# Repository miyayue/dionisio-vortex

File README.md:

# Projeto Dionísio
Esse projeto de IoT é o desafio de treinamento do laboratório de formação e inovação Vortex. O desafio consiste em construir uma mini adega de vinho inteligente, em que o usuário possa monitorar a temperatura e umidade dentro da adega e com controle de acesso por RFID ou controle remoto através de um Dashboard.

# Instruções
## Firmware
No VSCode, instale a extensão `PlatformIO`. Modifique os valores das variáveis `ssid` e `pswd` para o nome de sua rede WiFi e senha, respectivamente. Salve o arquivo e rode o comando `Upload and Monitor` para enviar o programa ao Esp32. 

## Dashboard
O dashboard pode ser visualizado em https://io.adafruit.com/letholanda/dashboards/dionisio-dashboard.

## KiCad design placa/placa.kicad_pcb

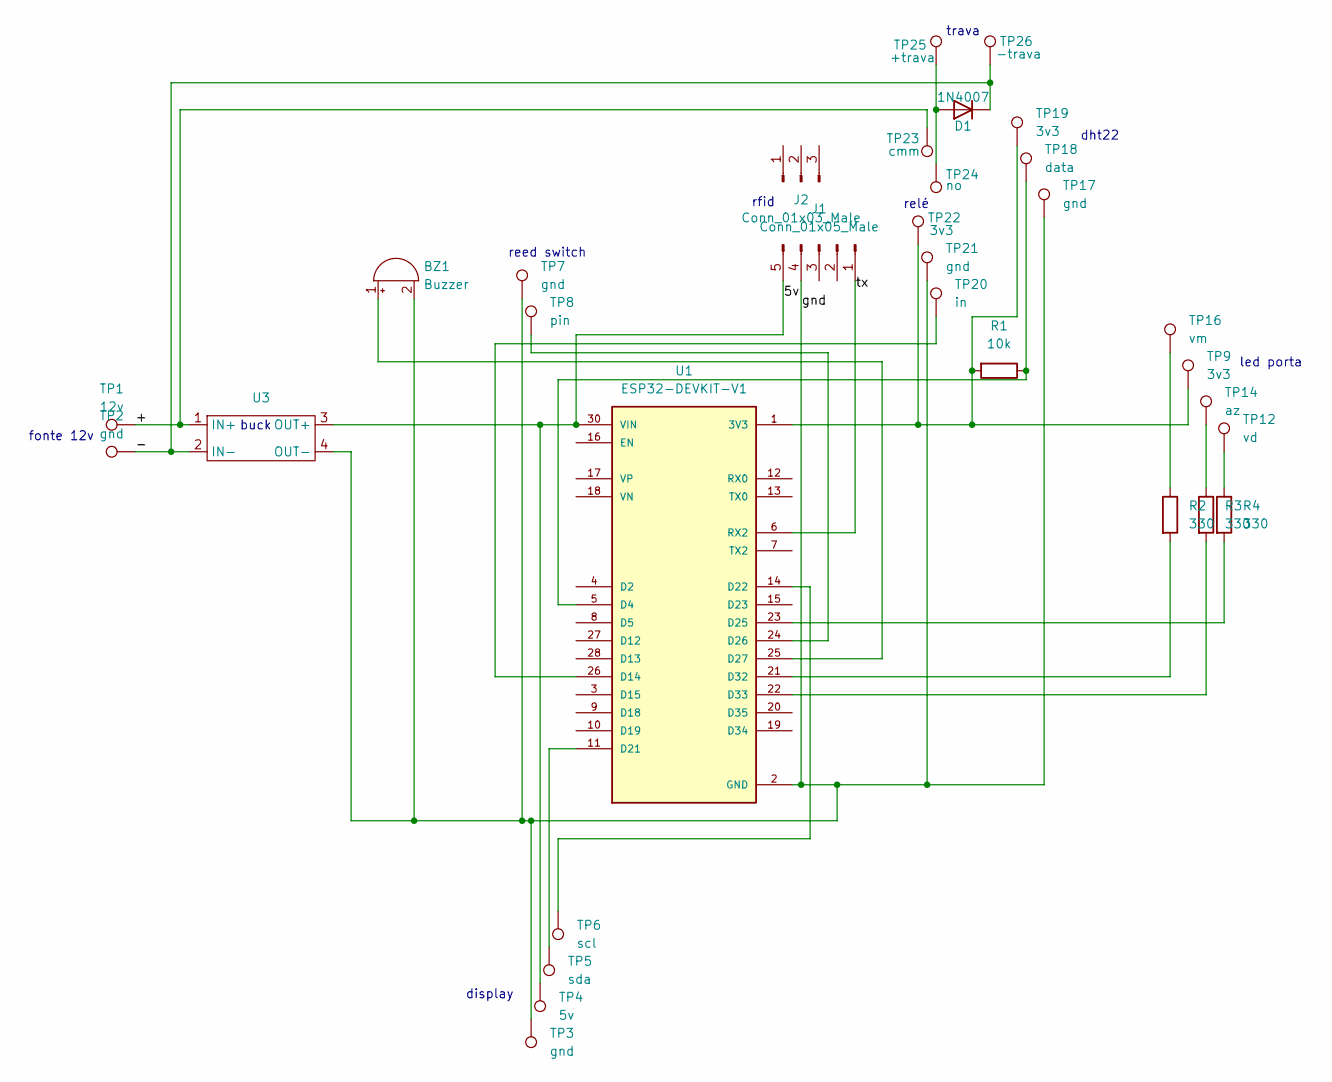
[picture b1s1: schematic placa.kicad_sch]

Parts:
BZ1: Buzzer; Buzzer_12x9.5RM7.6
D1: 1N4007; D_DO-41_SOD81_P10.16mm_Horizontal
J1: Conn_01x05_Male; PinSocket_1x05_P2.54mm_Vertical
J2: Conn_01x03_Male; PinSocket_1x03_P2.54mm_Vertical
R1: 10k; R_Axial_DIN0207_L6.3mm_D2.5mm_P7.62mm_Horizontal
R2, R3, R4: 330; R_Axial_DIN0207_L6.3mm_D2.5mm_P7.62mm_Horizontal
TP1: 12v; TestPoint_Pad_D3.0mm
TP2, TP3, TP7, TP17, TP21: gnd; TestPoint_Pad_D3.0mm
TP4: 5v; TestPoint_Pad_D3.0mm
TP5: sda; TestPoint_Pad_D3.0mm
TP6: scl; TestPoint_Pad_D3.0mm
TP8: pin; TestPoint_Pad_D3.0mm
TP9, TP19, TP22: 3v3; TestPoint_Pad_D3.0mm
TP12: vd; TestPoint_Pad_D3.0mm
TP14: az; TestPoint_Pad_D3.0mm
TP16: vm; TestPoint_Pad_D3.0mm
TP18: data; TestPoint_Pad_D3.0mm
TP20: in; TestPoint_Pad_D3.0mm
TP23: cmm; TestPoint_Pad_D3.0mm
TP24: no; TestPoint_Pad_D3.0mm
TP25: +trava; TestPoint_Pad_D3.0mm
TP26: -trava; TestPoint_Pad_D3.0mm
U1: ESP32-DEVKIT-V1; MODULE_ESP32_DEVKIT_V1; PARTREV N/A
U3: zk-qc-mini

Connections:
/5v: J1.5, TP4.1 (1_1), U1.30 (VIN), U3.3 (OUT+)
/+: TP1.1 (1_1), TP23.1 (1_1), U3.1 (IN+)
/-: D1.1 (K), TP2.1 (1_1), TP26.1 (1_1), U3.2 (IN-)
/tx: J1.1, U1.6 (RX2)
GND: BZ1.2 (+), J1.4, TP3.1 (1_1), TP7.1 (1_1), TP17.1 (1_1), TP21.1 (1_1), U1.2 (GND), U1.29 (GND), U3.4 (OUT-)
unnamed: BZ1.1 (-), U1.25 (D27)
unnamed: D1.2 (A), TP24.1 (1_1), TP25.1 (1_1)
unnamed: R2.1, TP16.1 (1_1)
unnamed: R3.1, TP14.1 (1_1)
unnamed: R4.1, TP12.1 (1_1)
unnamed: R1.2, TP9.1 (1_1), TP19.1 (1_1), TP22.1 (1_1), U1.1 (3V3)
unnamed: R1.1, TP18.1 (1_1), U1.5 (D4)
unnamed: TP20.1 (1_1), U1.26 (D14)
unnamed: TP5.1 (1_1), U1.11 (D21)
unnamed: TP6.1 (1_1), U1.14 (D22)
unnamed: R4.2, U1.23 (D25)
unnamed: TP8.1 (1_1), U1.24 (D26)
unnamed: R2.2, U1.21 (D32)
unnamed: R3.2, U1.22 (D33)

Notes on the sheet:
led porta
buck
fonte 12v
rfid
dht22
trava
relé
display
reed switch

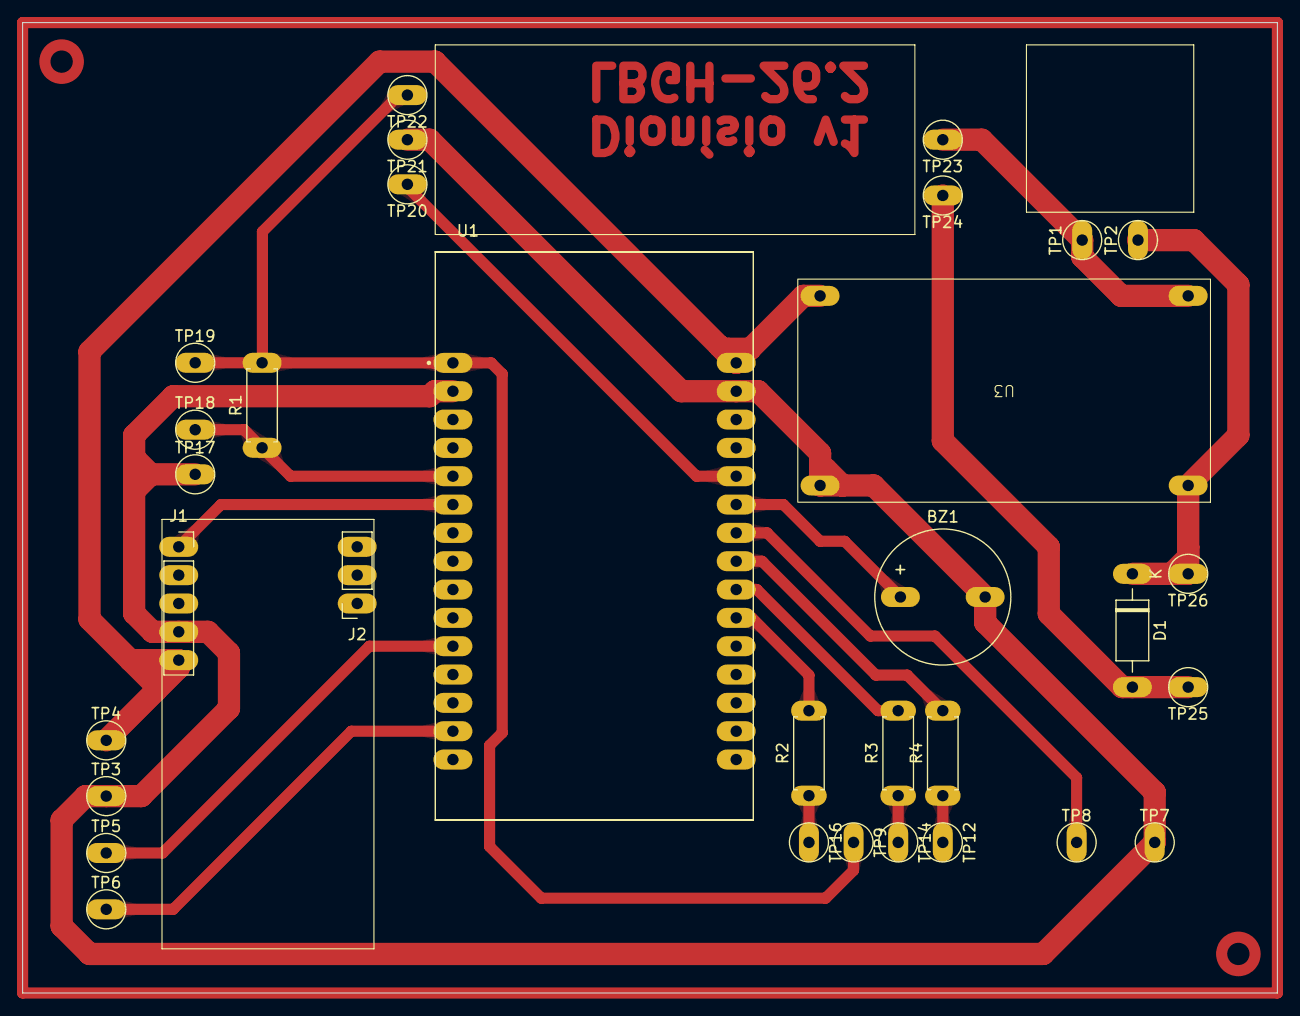
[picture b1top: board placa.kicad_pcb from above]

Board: 2 copper layers, 112.5 x 87.0 mm, 32 parts (0 on the bottom side), 19 nets.
